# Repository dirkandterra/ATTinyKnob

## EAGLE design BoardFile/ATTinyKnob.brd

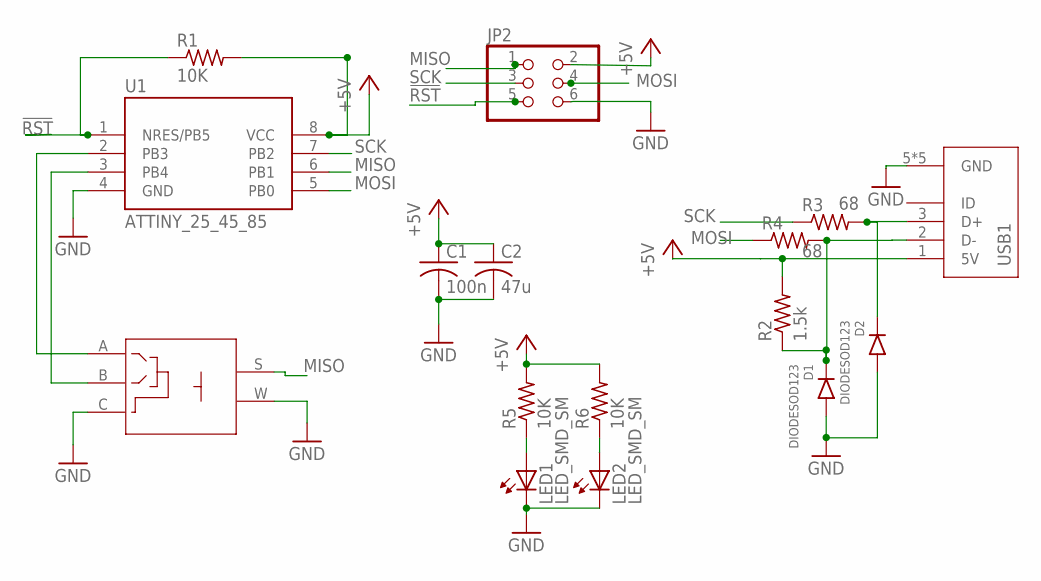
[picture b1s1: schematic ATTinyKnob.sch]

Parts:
C1: 100n; C0805
C2: 47u; C0805
D1, D2: DIODESOD123; SOD123
JP2: PINHD-2X3; 2X03
LED1, LED2: LED_SMD_SM
R1, R5, R6: 10K; M1206
R2: 1.5k; M1206
R3, R4: 68; M1206
ROT1: ROTARY_EC16
U1: ATTINY_25_45_85; SOIC-8
USB1: USB_MINIUSB_MINI_TH_RIGHTANG; USB_MINI_TH_RIGHTANGLE

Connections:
!RST: JP2.5, R1.1, U1.1 (NRES/PB5)
+5V: C1.1, C2.1, JP2.2, R1.2, R2.2, R5.2, R6.2, U1.8 (VCC), USB1.1 (5V)
GND: C1.2, C2.2, D1.1 (A), D2.1 (A), JP2.6, LED1.2 (C), LED2.2 (C), ROT1.C (COM), ROT1.W, U1.4 (GND), USB1.5 (GND), USB1.6 (GND), USB1.7 (GND), USB1.8 (GND), USB1.9 (GND)
MISO: JP2.1, ROT1.S, U1.6 (PB1)
MOSI: JP2.4, R4.1, U1.5 (PB0)
unnamed: ROT1.A, U1.2 (PB3)
unnamed: ROT1.B, U1.3 (PB4)
unnamed: D2.2 (C), R3.2, USB1.3 (D+)
unnamed: D1.2 (C), R2.1, R4.2, USB1.2 (D-)
unnamed: LED2.1 (A), R6.1
unnamed: LED1.1 (A), R5.1
SCK: JP2.3, R3.1, U1.7 (PB2)

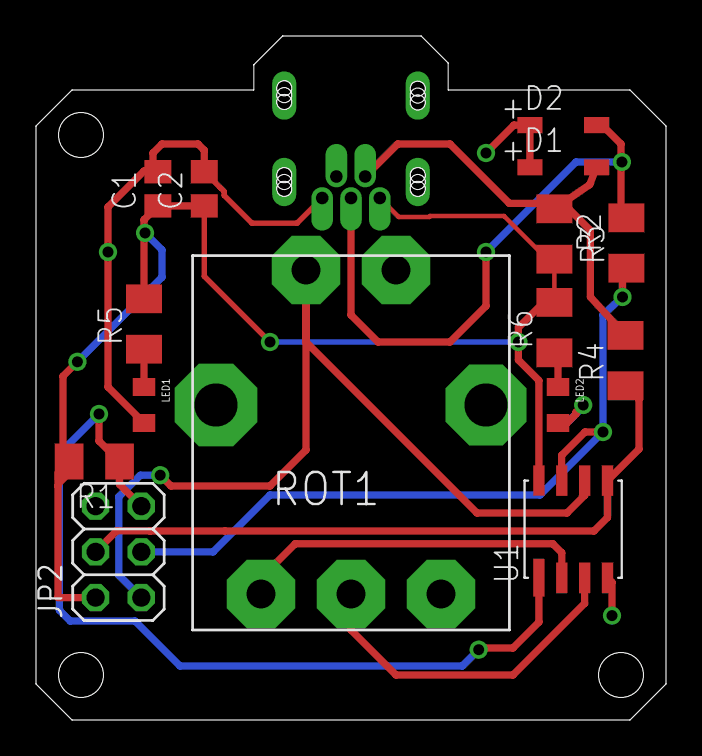
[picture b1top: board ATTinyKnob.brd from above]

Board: 2 copper layers, 35.0 x 38.0 mm, 16 parts (0 on the bottom side), 12 nets.

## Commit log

2024-09-07 Created board, added 3d files
2025-02-17 Added through hole usb
2025-02-18 Board built
2026-04-11 Changed file name
